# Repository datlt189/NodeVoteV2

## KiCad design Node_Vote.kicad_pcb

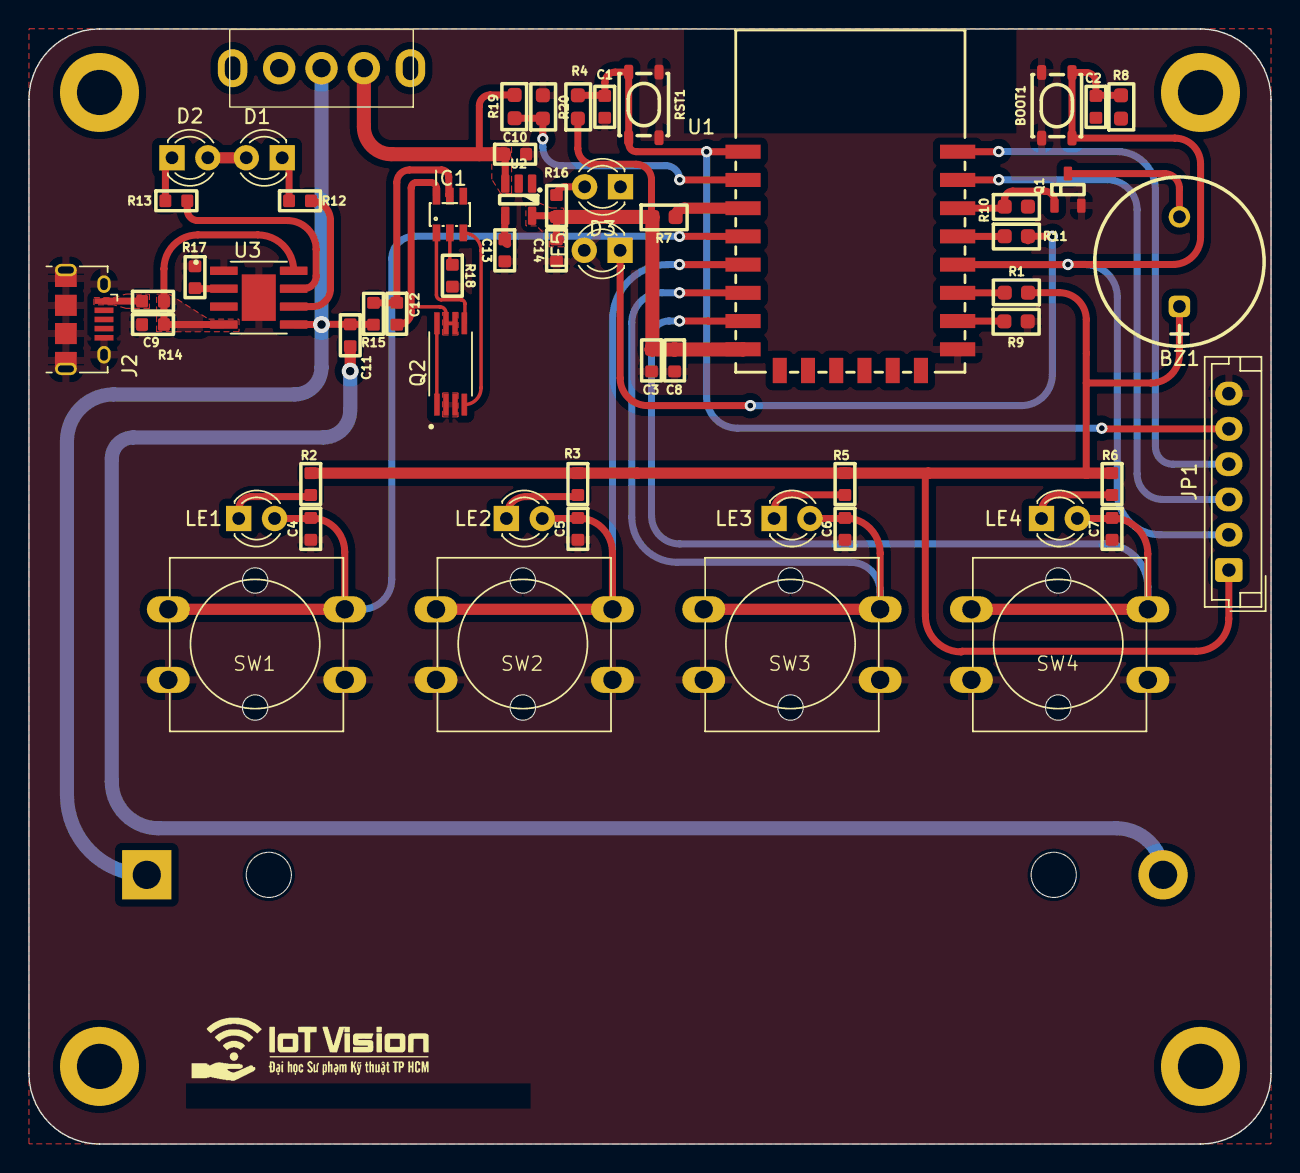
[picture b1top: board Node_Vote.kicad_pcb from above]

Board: 2 copper layers, 88.0 x 79.0 mm, 59 parts (1 on the bottom side), 39 nets.

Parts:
BOOT1: SW_Push; SW_SPST_PTS810
BT1: Battery_Cell; BatteryHolder_MPD_BH-18650-PC2
BZ1: Buzzer; Buzzer_GT111P
C1, C2, C4, C5, C6, C7, C12: 100nF; C_0603
C3, C9, C11: 10uF; C_0603
C8: 10nF; C_0603
C10, C13, C14: 1uF; C_0603
D1: GREEN; LED_D3.0mm_Red
D2: RED; LED_D3.0mm_Red
D3: BLUE; LED_D3.0mm_Red
IC1: DW01A; SOT23-6
J2: USB_B_Micro; USB_Micro-B_Amphenol_10118194_Horizontal
JP1: Conn_JST_SMD_6P; JST_EH_B6B-EH-A_1x06_P2.50mm_Vertical
LE1, LE2, LE3, LE4: GREEN; LED_D3.0mm_Red
LE5: RED; LED_D3.0mm_Red
Q1: N_Mosfet; SOT23-3
Q2: FS8205A; SOP65P640X120-8N
R1, R4, R7, R8, R9, R10: 10K; R0603
R2, R3, R5, R6: 10K; R_0603
R11: 1K5; R0603
R12, R13: 1K5; R_0603
R14: 0.5R; R_0603
R15: 100R; R_0603
R16, R18: 1K; R_0603
R17: 2K; R_0603
R19: 3k3; R0603
R20: 1K; R0603
RST1: SW_Push; SW_SPST_PTS810
S1: EG1206; SS-12F23G6
SW1, SW2, SW3, SW4: SW_Push; 12x12mm_Omron
U1: ESP-07; ESP8266-07__ESP32-C3-12F
U2: RT9193-33GB; SOT23-5
U3: TP4056

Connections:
+3V3: BZ1.1 (-), C3.1, C8.1, C14.1, JP1.1, R1.1, R2.1, R3.1, R4.1, R5.1, R6.1, R7.1, R8.1, R16.2, U1.8 (VCC), U2.5 (VOUT)
/BUTTON/BTA: C4.1, LE1.2, SW1.2, U1.4 (GPIO16)
/BUTTON/BTB: C5.1, LE2.2, SW2.2, U1.5 (GPIO14)
/BUTTON/BTC: C6.1, LE3.2, SW3.2, U1.6 (GPIO12)
/BUTTON/BTD: C7.1, LE4.2, SW4.2, U1.7 (GPIO13)
/POWER/ADC_BAT: C10.1, R19.1, S1.1, U2.1 (VIN), U2.3 (EN)
/POWER/BAT+: BT1.1 (+), C11.1, R15.1, S1.2, U3.5 (BAT)
/POWER/BAT-: BT1.2 (-), C11.2, C12.2, IC1.6 (GND), Q2.6, Q2.7
/POWER/CHRG: R13.2, U3.7 (~CHRG)
/POWER/STDBY: R12.2, U3.6 (~STDBY)
/POWER/VBUS: C9.2, D1.2 (A), D2.2 (A), R14.2, U3.4 (VCC), U3.8 (CE)
/esp8266/ADC: R19.2, R20.1, U1.2 (ADC)
/esp8266/BOOT: BOOT1.1, C2.1, JP1.2, R8.2, U1.18 (GPIO0)
/esp8266/Buzzer: Q1.1 (G), R10.1, U1.20 (GPIO5)
/esp8266/EN: R7.2, U1.3 (EN)
/esp8266/GPIO2: R1.2, U1.17 (GPIO2)
/esp8266/Led_BAT: R11.1, U1.19 (GPIO4)
/esp8266/RST: C1.1, JP1.5, R4.2, RST1.1, U1.1 (~RST)
/esp8266/RXD: JP1.3, U1.21 (GPIO3/RXD)
/esp8266/TXD: JP1.4, U1.22 (GPIO1/TXD)
GND: BOOT1.2, C1.2, C2.2, C3.2, C4.2, C5.2, C6.2, C7.2, C8.2, C9.1, C10.2, C13.2, C14.2, D3.1 (K), J2.5 (GND), J2.6 (Shield), JP1.6, LE5.2, Q1.2 (S), Q2.2, Q2.3, R9.2, R10.2, R17.1, R18.2, R20.2, RST1.2, SW1.1, SW2.1, SW3.1, SW4.1, U1.15 (GND), U2.2 (GND), U3.1 (TEMP), U3.3 (GND), U3.9 (EP)
unnamed: BZ1.2 (+), Q1.3 (D)
unnamed: D1.1 (K), R12.1
unnamed: D2.1 (K), R13.1
unnamed: D3.2 (A), R16.1
unnamed: IC1.2 (CS), R18.1
unnamed: IC1.3 (OC), Q2.4
unnamed: IC1.1 (OD), Q2.5
unnamed: C12.1, IC1.5 (VCC), R15.2
unnamed: J2.1 (VBUS), R14.1
unnamed: LE1.1, R2.2
unnamed: LE2.1, R3.2
unnamed: LE3.1, R5.2
unnamed: LE4.1, R6.2
unnamed: LE5.1, R11.2
unnamed: Q2.1, Q2.8
unnamed: R9.1, U1.16 (GPIO15)
unnamed: C13.1, U2.4 (BP)
unnamed: R17.2, U3.2 (PROG)

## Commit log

2023-07-14 Update NodeVote V2
